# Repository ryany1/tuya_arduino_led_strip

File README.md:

This project is developed using Tuya SDK, which enables you to quickly develop
branded apps connecting and controlling smart scenarios of many devices.
For more information, please check Tuya Developer Website.

# tuya_arduino_led_strip
该项目为arduino+tuya搭建的幻彩灯带，共有两个方案实现功能

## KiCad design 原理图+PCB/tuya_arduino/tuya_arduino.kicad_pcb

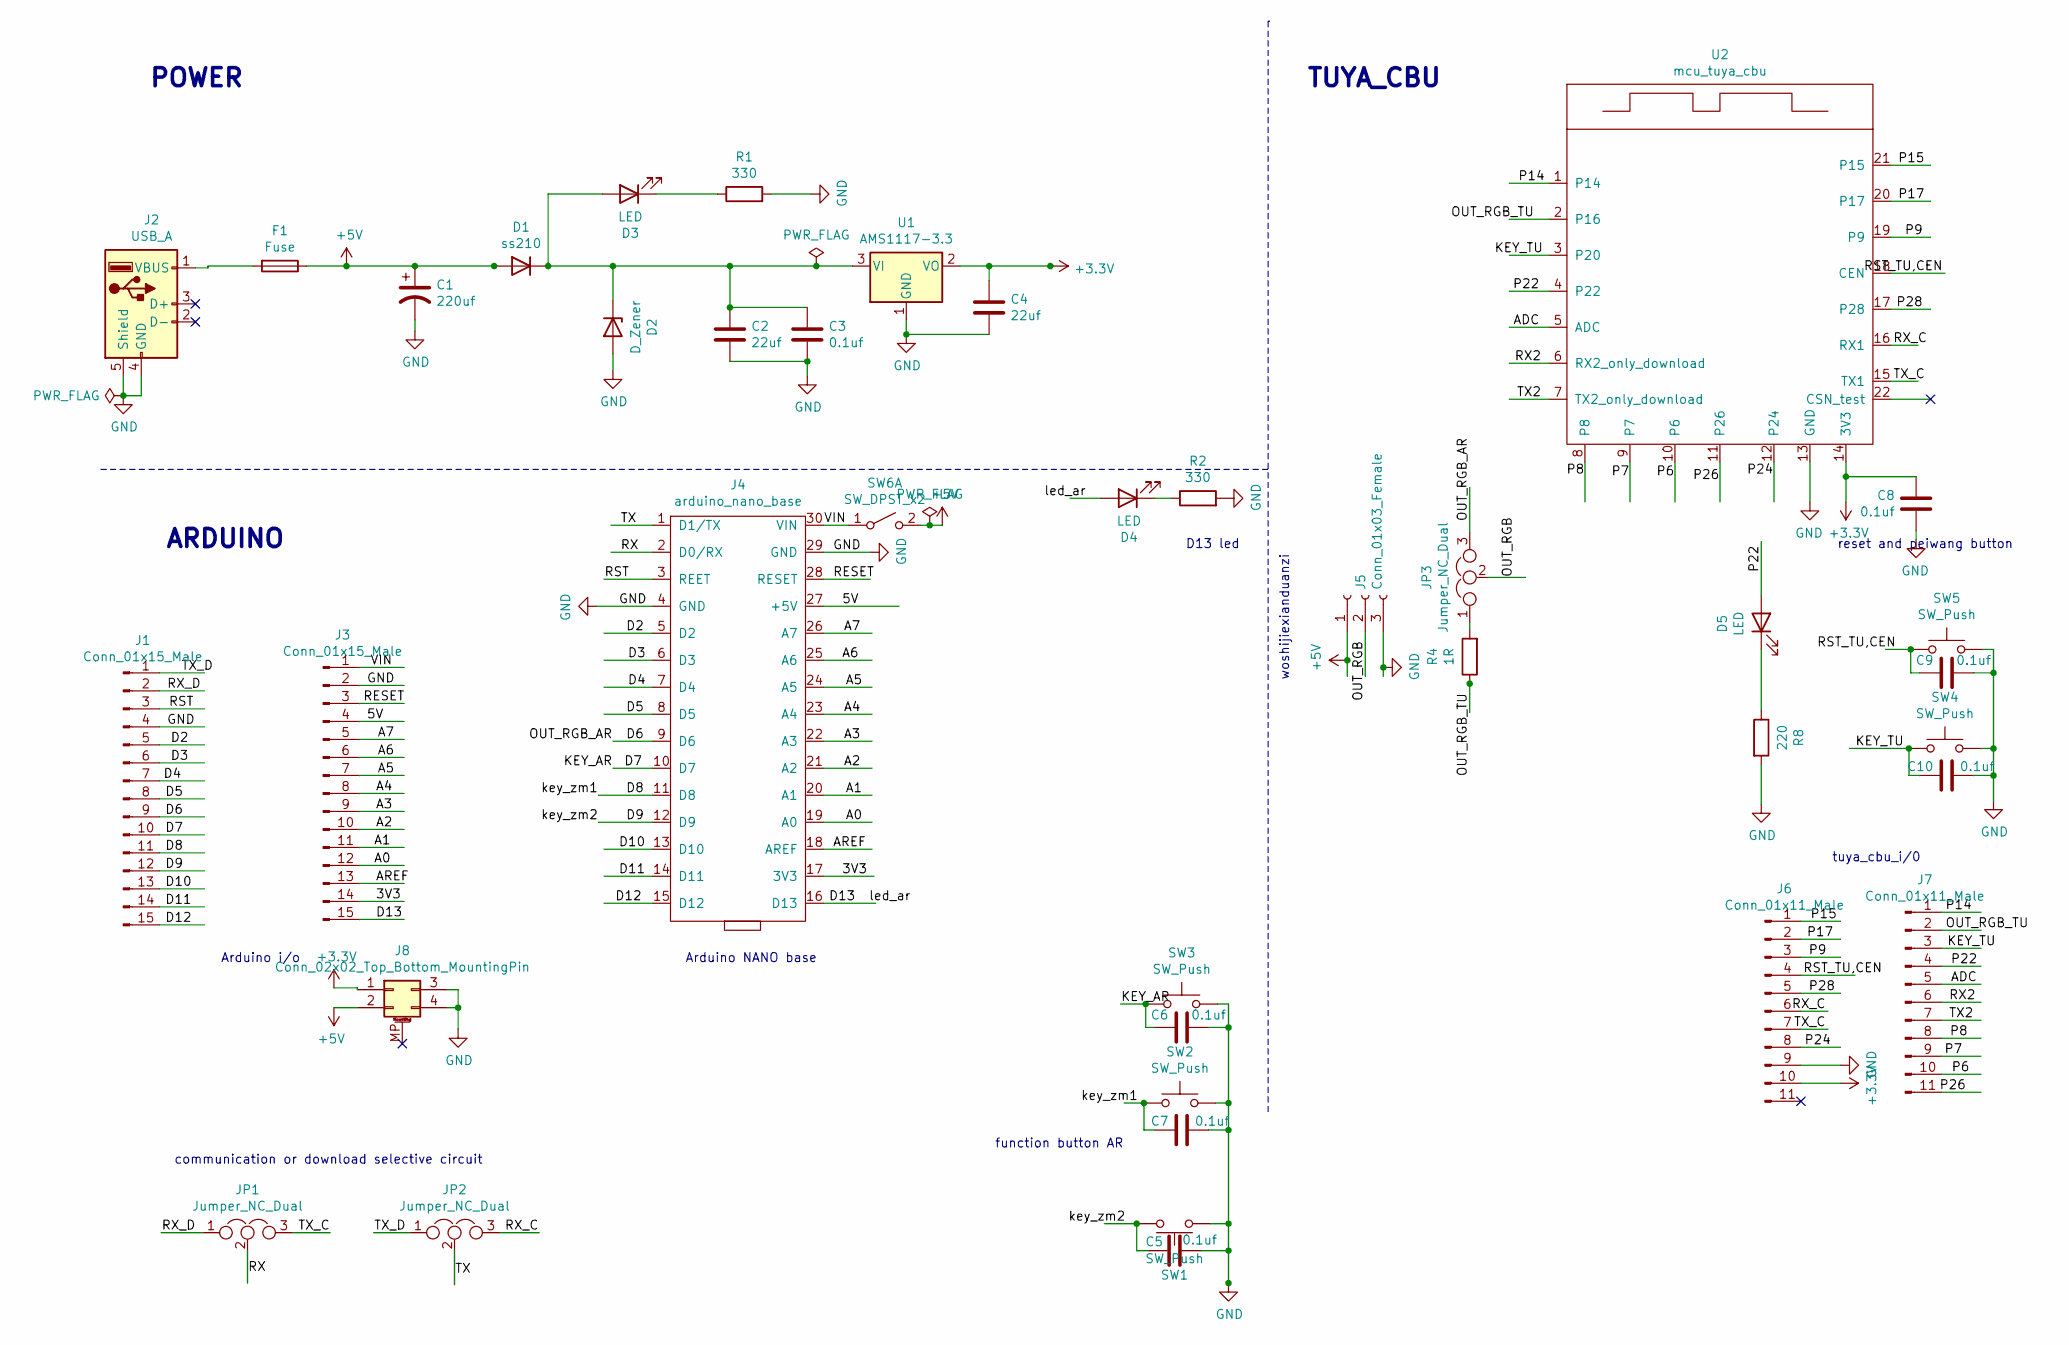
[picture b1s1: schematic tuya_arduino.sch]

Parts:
C1: 220uf; CP_Radial_D6.3mm_P2.50mm
C2, C4: 22uf; CP_EIA-3216-18_Kemet-A_Pad1.58x1.35mm_HandSolder
C3, C5, C6, C7, C8, C9, C10: 0.1uf; C_0603_1608Metric_Pad1.08x0.95mm_HandSolder
D1: ss210; D_SMA_Handsoldering
D2: D_Zener; D_SMB_Handsoldering
D3, D4, D5: LED; LED_0603_1608Metric_Pad1.05x0.95mm_HandSolder
F1: Fuse; Fuse_0805_2012Metric_Pad1.15x1.40mm_HandSolder
J1, J3: Conn_01x15_Male; PinHeader_1x15_P2.54mm_Vertical
J2: USB_A; MicroUSB_5S_B_A01SB141B1-067
J4: arduino_nano_base; Arduino_nano_base
J5: Conn_01x03_Female; PinHeader_1x03_P2.54mm_Vertical
J6, J7: Conn_01x11_Male; PinHeader_1x11_P2.54mm_Vertical
J8: Conn_02x02_Top_Bottom_MountingPin; PinHeader_2x02_P2.54mm_Vertical
JP1, JP2, JP3: Jumper_NC_Dual; PinHeader_1x03_P2.54mm_Vertical
R1, R2: 330; R_0603_1608Metric_Pad0.98x0.95mm_HandSolder
R4: 1R; R_0603_1608Metric_Pad0.98x0.95mm_HandSolder
R8: 220; R_0603_1608Metric_Pad0.98x0.95mm_HandSolder
SW1, SW2, SW3, SW4, SW5: SW_Push; button_smd
SW6: SW_DPST_x2; SW_SPST_B3U-1000P
U1: AMS1117-3.3; SOT-223-3_TabPin2
U2: mcu_tuya_cbu; tuya_cbu

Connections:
+3V3: C4.1, C8.1, J6.10, J8.1, U1.2 (VO), U2.14 (3V3)
+5V: C1.1, D1.2 (A), F1.1, J5.1, J8.2, SW6.2 (B)
/3V3: J3.14, J4.17 (3V3)
/5V: J3.4, J4.27 (+5V)
/A0: J3.12, J4.19 (A0)
/A1: J3.11, J4.20 (A1)
/A2: J3.10, J4.21 (A2)
/A3: J3.9, J4.22 (A3)
/A4: J3.8, J4.23 (A4)
/A5: J3.7, J4.24 (A5)
/A6: J3.6, J4.25 (A6)
/A7: J3.5, J4.26 (A7)
/ADC: J7.5, U2.5 (ADC)
/AREF: J3.13, J4.18 (AREF)
/D2: J1.5, J4.5 (D2)
/D3: J1.6, J4.6 (D3)
/D4: J1.7, J4.7 (D4)
/D5: J1.8, J4.8 (D5)
/D6: J1.9, J4.9 (D6), JP3.3
/D7: C6.1, J1.10, J4.10 (D7), SW3.1
/D8: C7.1, J1.11, J4.11 (D8), SW2.1
/D9: C5.1, J1.12, J4.12 (D9), SW1.1
/D10: J1.13, J4.13 (D10)
/D11: J1.14, J4.14 (D11)
/D12: J1.15, J4.15 (D12)
/D13: D4.2 (A), J3.15, J4.16 (D13)
/KEY_TU: C10.1, J7.3, SW4.1, U2.3 (P20)
/OUT_RGB: J5.2, JP3.2
/OUT_RGB_TU: J7.2, R4.1, U2.2 (P16)
/P6: J7.10, U2.10 (P6)
/P7: J7.9, U2.9 (P7)
/P8: J7.8, U2.8
/P9: J6.3, U2.19 (P9)
/P14: J7.1, U2.1 (P14)
/P15: J6.1, U2.21 (P15)
/P17: J6.2, U2.20 (P17)
/P22: D5.2 (A), J7.4, U2.4 (P22)
/P24: J6.8, U2.12 (P24)
/P26: J7.11, U2.11 (P26)
/P28: J6.5, U2.17 (P28)
/RESET: J3.3, J4.28 (RESET)
/RST: J1.3, J4.3 (REET)
/RST_TU,CEN: C9.1, J6.4, SW5.1, U2.18 (CEN)
/RX: J4.2 (D0/RX), JP1.2
/RX2: J7.6, U2.6 (RX2_only_download)
/RX_C: J6.6, JP2.3, U2.16 (RX1)
/RX_D: J1.2, JP1.1
/TX: J4.1 (D1/TX), JP2.2
/TX2: J7.7, U2.7 (TX2_only_download)
/TX_C: J6.7, JP1.3, U2.15 (TX1)
/TX_D: J1.1, JP2.1
/VIN: J3.1, J4.30 (VIN), SW6.1 (A)
GND: C1.2, C2.2, C3.2, C4.2, C5.2, C6.2, C7.2, C8.2, C9.2, C10.2, D2.2 (A), J1.4, J2.4 (GND), J2.5 (Shield), J3.2, J4.4 (GND), J4.29 (GND), J5.3, J6.9, J8.3, J8.4, R1.2, R2.2, R8.2, SW1.2, SW2.2, SW3.2, SW4.2, SW5.2, U1.1 (GND), U2.13 (GND)
unnamed: C2.1, C3.1, D1.1 (K), D2.1 (K), D3.2 (A), U1.3 (VI)
unnamed: D3.1 (K), R1.1
unnamed: D4.1 (K), R2.1
unnamed: D5.1 (K), R8.1
unnamed: F1.2, J2.1 (VBUS)
unnamed: JP3.1, R4.2

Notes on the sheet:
POWER
ARDUINO
TUYA_CBU
Arduino i/o
communication or download selective circuit
Arduino NANO base
D13 led
function button AR
tuya_cbu_i/0
reset and peiwang button
woshijiexianduanzi

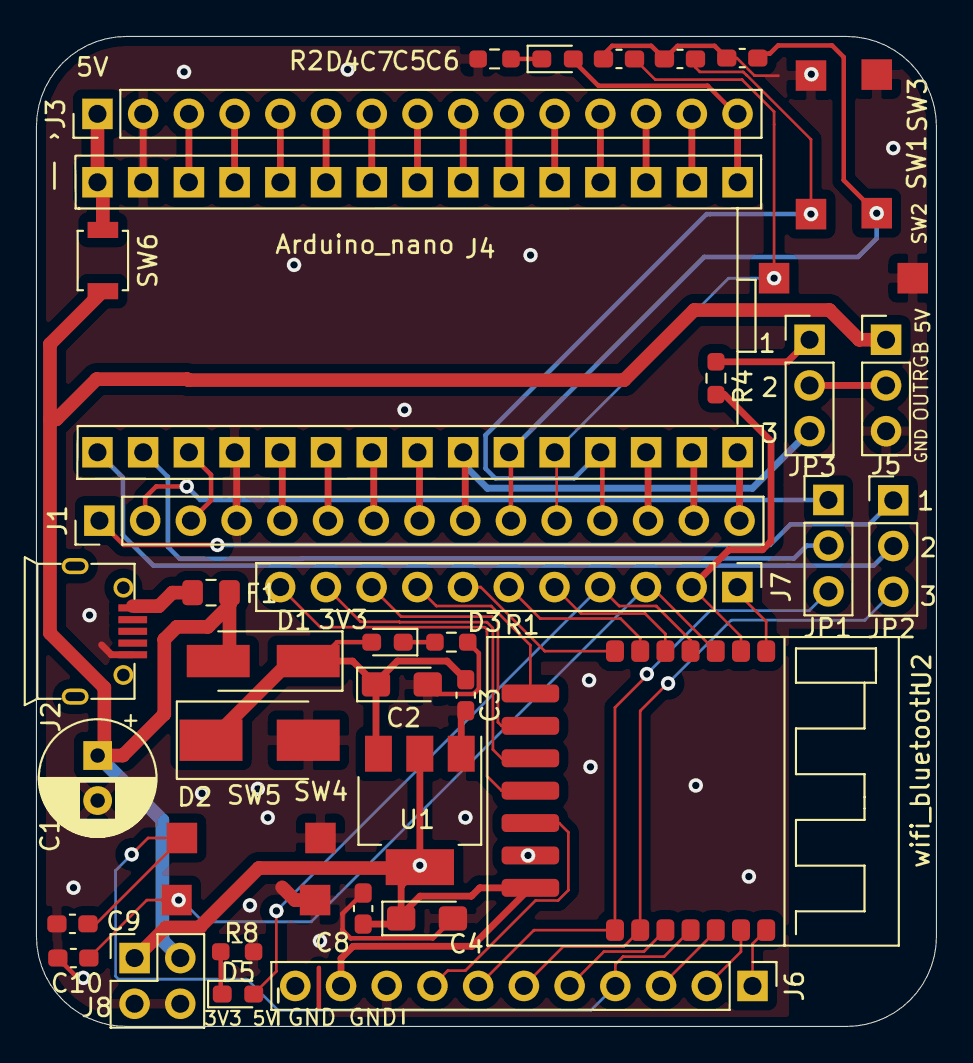
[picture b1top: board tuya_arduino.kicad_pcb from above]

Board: 2 copper layers, 50.0 x 55.0 mm, 39 parts (0 on the bottom side), 59 nets.

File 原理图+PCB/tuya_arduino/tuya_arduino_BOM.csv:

"Comment","Description","Designator","Footprint","LibRef","Pins","Quantity","PartNumber","url",
"22uf","desc","C2,C4,","CP_EIA-3216-18_Kemet-A_Pad1.58x1.35mm_HandSolder","libref","2","2","","",
"0.1uf","desc","C3,C5,C6,C7,C8,C9,C10,","C_0603_1608Metric_Pad1.08x0.95mm_HandSolder","libref","2","7","","",
"ss210","desc","D1,","D_SMA_Handsoldering","libref","2","1","","",
"D_Zener","desc","D2,","D_SMB_Handsoldering","libref","2","1","","",
"LED","desc","D3,D4,D5,","LED_0603_1608Metric_Pad1.05x0.95mm_HandSolder","libref","2","3","","",
"Fuse","desc","F1,","Fuse_0805_2012Metric_Pad1.15x1.40mm_HandSolder","libref","2","1","","",
"S8050","desc","Q1,","SOT-23","libref","3","1","","",
"330","desc","R1,R2,","R_0603_1608Metric_Pad0.98x0.95mm_HandSolder","libref","2","2","","",
"2k","desc","R3,R6,R7,","R_0603_1608Metric_Pad0.98x0.95mm_HandSolder","libref","2","3","","",
"1R","desc","R4,","R_0603_1608Metric_Pad0.98x0.95mm_HandSolder","libref","2","1","","",
"NC/0R","desc","R5,","R_0603_1608Metric_Pad0.98x0.95mm_HandSolder","libref","2","1","","",
"220","desc","R8,","R_0603_1608Metric_Pad0.98x0.95mm_HandSolder","libref","2","1","","",
"AMS1117-3.3","desc","U1,","SOT-223-3_TabPin2","libref","4","1","","",
"mcu_tuya_cbu","desc","U2,","tuya_cbu","libref","21","1","","",
"SW_Push","desc","SW1,SW2,SW3,SW4,SW5,","button_smd","libref","2","5","","",
"LOGO","desc","G***,","tuya-logo","libref","0","1","","",
"KiCad-Logo_6mm_Copper","desc","REF**,","KiCad-Logo_6mm_Copper","libref","0","1","","",
"Through Hole Items ",
"220uf","desc","C1,","CP_Radial_D6.3mm_P2.50mm","libref","2","1","","",
"Conn_01x15_Male","desc","J1,J3,","PinHeader_1x15_P2.54mm_Vertical","libref","15","2","","",
"USB_A","desc","J2,","MicroUSB_5S_B_A01SB141B1-067","libref","9","1","","",
"arduino_nano_base","desc","J4,","Arduino_nano_base","libref","30","1","","",
"Conn_01x03_Female","desc","J5,","PinHeader_1x03_P2.54mm_Vertical","libref","3","1","","",
"Conn_01x11_Male","desc","J6,J7,","PinHeader_1x11_P2.54mm_Vertical","libref","11","2","","",
"Conn_02x02_Top_Bottom_MountingPin","desc","J8,","PinHeader_2x02_P2.54mm_Vertical","libref","4","1","","",
"Jumper_NC_Dual","desc","JP1,JP2,JP3,","PinHeader_1x03_P2.54mm_Vertical","libref","3","3","","",
"HOLE_2MM","desc","REF**,","HOLE_2MM","libref","1","1","","",
"MP_HOLE_L4_M3","desc","REF**,","MP_HOLE_L4_M3","libref","1","1","","",

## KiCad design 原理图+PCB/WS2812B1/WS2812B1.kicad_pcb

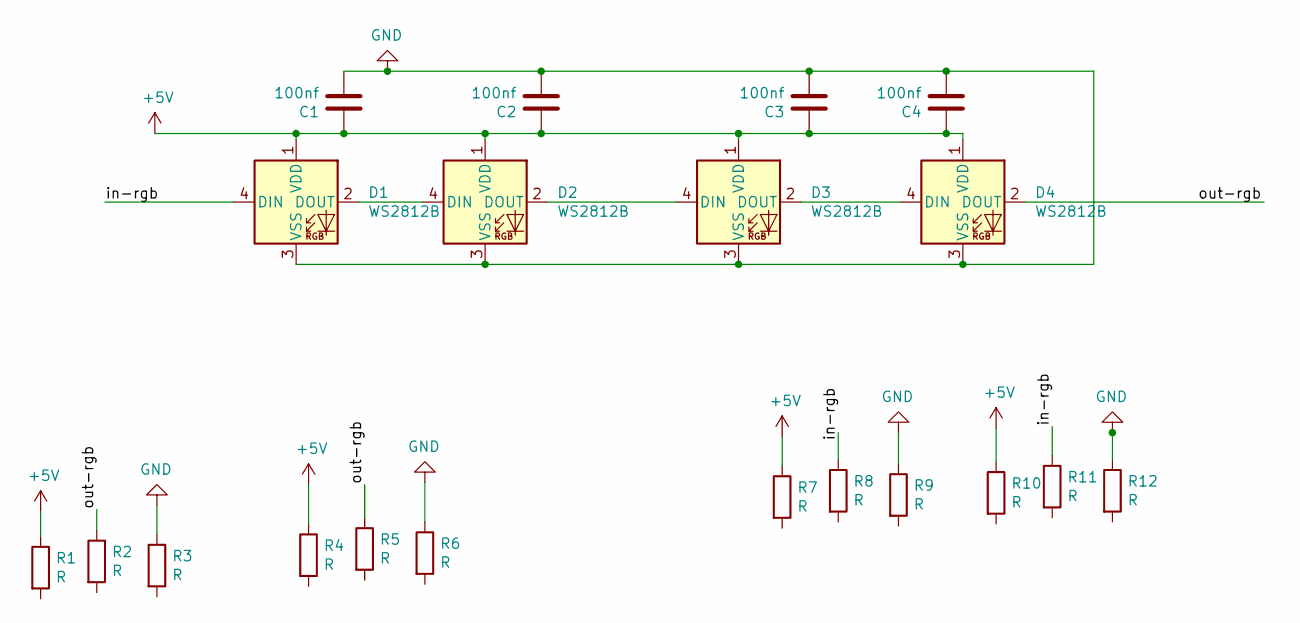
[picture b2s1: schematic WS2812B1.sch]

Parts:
C1, C2, C3, C4: 100nf; C_0603_1608Metric_Pad1.08x0.95mm_HandSolder
D1, D2, D3, D4: WS2812B; LED_WS2812B_PLCC4_5.0x5.0mm_P3.2mm
R1, R2, R3, R4, R5, R6, R7, R8, R9, R10, R11, R12: R; 焊接连接电阻

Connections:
+5V: C1.1, C2.1, C3.1, C4.1, D1.1 (VDD), D2.1 (VDD), D3.1 (VDD), D4.1 (VDD), R1.1, R4.1, R7.1, R10.1
/in-rgb: D1.4 (DIN), R8.1, R11.1
/out-rgb: D4.2 (DOUT), R2.1, R5.1
GND: C1.2, C2.2, C3.2, C4.2, D1.3 (VSS), D2.3 (VSS), D3.3 (VSS), D4.3 (VSS), R3.1, R6.1, R9.1, R12.1
unnamed: D1.2 (DOUT), D2.4 (DIN)
unnamed: D2.2 (DOUT), D3.4 (DIN)
unnamed: D3.2 (DOUT), D4.4 (DIN)

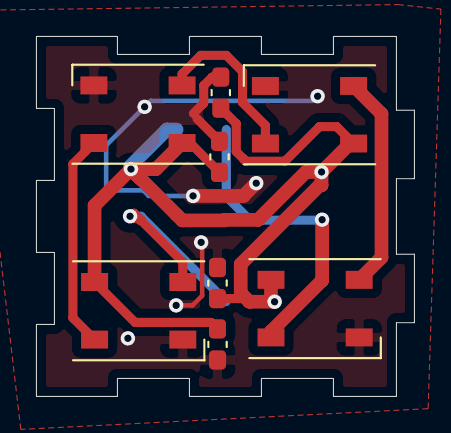
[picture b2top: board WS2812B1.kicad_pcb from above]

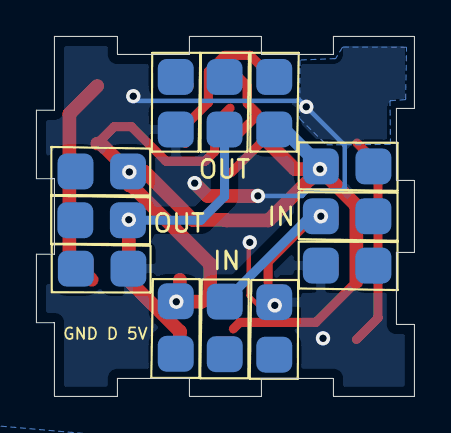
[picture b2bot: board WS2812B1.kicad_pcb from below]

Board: 2 copper layers, 21.0 x 20.0 mm, 20 parts (12 on the bottom side), 7 nets.

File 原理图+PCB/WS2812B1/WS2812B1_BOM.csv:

"Comment","Description","Designator","Footprint","LibRef","Pins","Quantity","PartNumber","url",
"100nf","desc","C1,C2,C3,C4,","C_0603_1608Metric_Pad1.08x0.95mm_HandSolder","libref","2","4","","",
"WS2812B","desc","D1,D2,D3,D4,","LED_WS2812B_PLCC4_5.0x5.0mm_P3.2mm","libref","4","4","","",
"Through Hole Items ",
"R","desc","R1,R2,R3,R4,R5,R6,R7,R8,R9,R10,R11,R12,","焊接连接电阻","libref","2","12","","",

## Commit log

2021-06-08 second commit,新增截图
2021-06-14 seconed commit
